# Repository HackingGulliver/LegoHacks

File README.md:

# LegoHacks
Alles rund um Lego und Elektronik.

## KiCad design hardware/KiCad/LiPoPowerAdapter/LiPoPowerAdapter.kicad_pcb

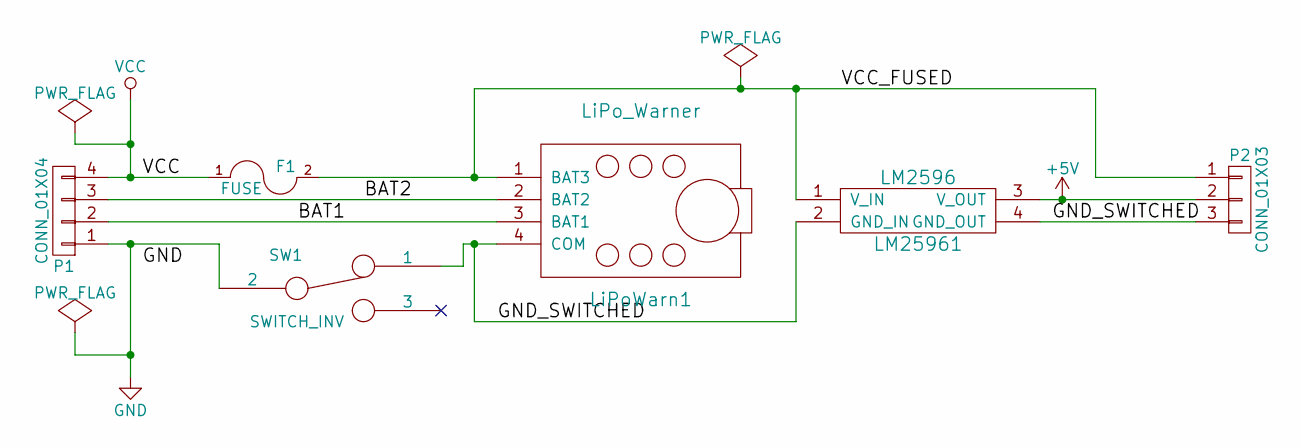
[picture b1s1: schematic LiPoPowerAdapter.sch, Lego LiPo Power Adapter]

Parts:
F1: FUSE; FKS-Halter
LM25961: LM2596
LiPoWarn1: LiPo_Warner; Pin_Header_Straight_1x04
P1: CONN_01X04; JST_XH_S04B-XH-A_04x2.50mm_Angled
P2: CONN_01X03; Pin_Header_Angled_1x03
SW1: SWITCH_INV; AS500APC-Kippschalter

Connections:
+5V: LM25961.3 (V_OUT), P2.2
/BAT1: LiPoWarn1.3 (BAT1), P1.2
/BAT2: LiPoWarn1.2 (BAT2), P1.3
/GND_SWITCHED: LM25961.2 (GND_IN), LM25961.4 (GND_OUT), LiPoWarn1.4 (COM), P2.3, SW1.1
/VCC_FUSED: F1.2, LM25961.1 (V_IN), LiPoWarn1.1 (BAT3), P2.1
GND: P1.1, SW1.2
VCC: F1.1, P1.4

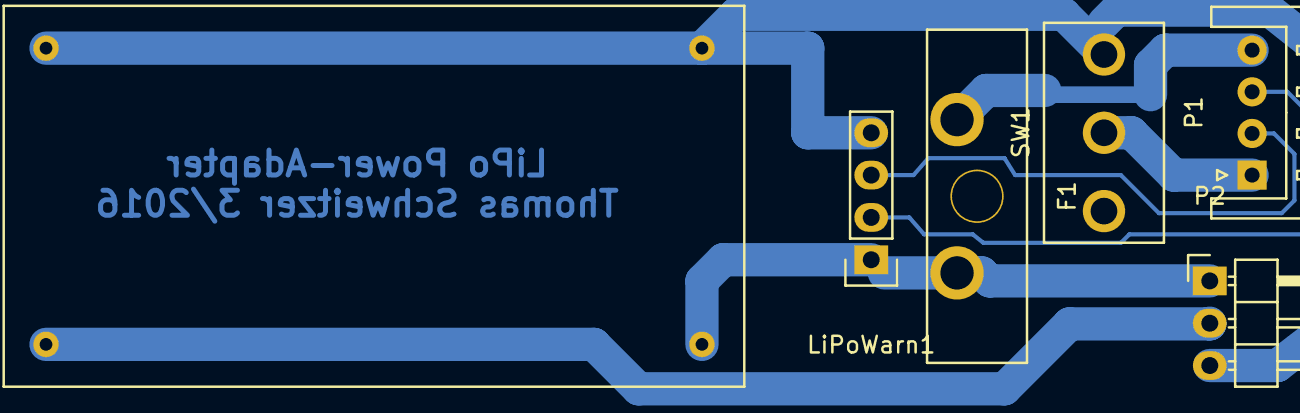
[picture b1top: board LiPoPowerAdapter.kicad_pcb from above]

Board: 2 copper layers, 6 parts (0 on the bottom side), 7 nets.

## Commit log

2016-02-25 Untertitel des Repos angepasst
2016-03-30 KiCad-Projekt mit LiPo-PowerAdapter hinzugefügt
2016-04-01 Erste Version der Stepper-Library zum Ansteuern von Schrittmotoren.
2016-04-01 LiPoPowerAdapter unter Linux mit KiCad bearbeitet
2016-04-03 Möglichkeit zum Debuggen hinzugefügt. Siehe geänderten Kommentar für eine Anleitung.
2016-04-05 Erste Version der SerialDriver-Hardware (KiCad) hinzugefügt
2016-04-05 .gitignore hinzugefügt
2016-04-05 SerialDriver Arduino-Projekt hinzugefügt
2016-04-05 Bauteil ULN2803 zur Bibliothek legohacks.lib hinzugefügt
2016-04-07 Erste Version des SerialDrivers mit Shift-Register und PWM. digitalWrite war sehr langsam und musste durch fastDigitalWrite ersetzt werden. Dies kann noch weiter optimiert werden.
2016-04-08 Optimierung beim Rausschreiben der Bits ins Schieberegister. Die Version ist ca. 14 mal schneller.
2016-04-08 Berechnung von PWM-Bitmustern für das Schieberegister in der Klasse PWMStateCalculator. Damit wird ein Lauflicht mit nachlassender Helligkeit realisiert.
2016-04-09 Shiftregister wird mittels SPI angesteuert
2016-04-09 Anpassungen für Benchmark mit SPI
2016-04-09 Anpassungen für Benchmark mit Bit Bang
2016-04-09 Überflüssigen Befehl entfernt
2016-04-09 Bit-Reihenfolge beim SPI-Transfer umgekehrt
2016-04-11 Aufruf der PWM-Schritte aus Timer heraus.
2016-04-12 Refaktorisierung mit neuen Methoden
2016-04-12 Erste Performance Messergebnisse
2016-04-12 Benchmarks und Optimierung für den PWMStateCalculator.
2016-04-13 Benchmarks zur Auswertung der Last durch die PWM-Timer erweitert.
2016-04-13 Benchmarks dokumentiert für Ist-Zustand und das Optimum, bei dem ohne Berechnung die Daten direkt gesendet werden.
2016-04-14 Erster Entwurf des vorberechnenden PWMStateCalculators
2016-04-15 Fine-Tuning am Algorithmus zur Berechnung der zu sendenden Daten.
2016-04-15 Funktionierende Version des vorberechnenden State-Calculators
2016-04-15 Benchmarks in eigene Datei ausgelagert.
2016-04-15 Optimierung des vorberechnenden PWMStateCalculators. (Version 2 in den Benchmarks).
2016-04-16 Benchmark zur Messung der Zeit in der die zu sendenden Daten berechnet werden.
2016-04-16 Berechnung der Daten optimiert (im Benchmark Version 3)
2016-04-16 Schleife zur Berechnung der Daten optimiert (Version 4)
2016-04-16 Commented and cleaned up the code. Moved some initialization to the PWMStateCalculator.
2016-04-16 RGB-LED Test
2016-04-16 Bitreihenfolge im PWMStateCalculator geändert.
2016-04-18 Die zu sendenden Daten werden jeweils nur für den aktuellen Schritt vorberechnet, falls Duty-Einstellungen geändert wurden.
2016-04-19 Die Klassen PWMController und PowerController wurden hinzugefügt. Der PWMController übernimmt das Setup des Timers und steuert damit den PWMStateCalculator an.
2016-04-19 Die Methoden setDuty() und allDutiesSet() werden nun direkt vom PowerController implementiert. Sie delegieren an den chainedController.
2016-04-19 Klasse RGBLed hinzugefügt.
2016-04-19 Erste Version mit MsTimer2 zur Ansteuerung des TimedPowerControllers
2016-04-19 TimedPowerController als abstrakte Klasse und Pulse als eine konkrete Implementierung hinzugefügt. Pulse ist bisher nur rudimentär.
2016-04-25 Erste Version des TimerPowerControllers "Pulse" mit Fixed Point Arithmetic
2016-04-25 Pulse mit Dreieckssignal und wenigen floating point Berechnungen.
2016-04-26 Pulsweite kann in der Klasse Pulse gesetzt werden.
2016-04-26 Pulse unterstützt die Wellenformen Sägezahn, Dreieck und Blinken.
2016-04-27 Code cleanup in Klasse Pulse
2016-06-02 Im Beispielprogramm vom SerialDriver wird nach der Änderung der LED-Farbe die Pulsweite gesetzt, damit die Änderungen wirksam werden.
2016-06-02 Neue Projekte zum Experimentieren mit der VirtualWire-Lib hinzugefügt. Senden und Empfangen mit dem mitgelieferten Beispielcode ist damit möglich.
2016-06-07 Initiale Version des VirtualWireReceivers mit TimerOne als Basis-Lib für Timer
2016-06-07 VirtualWire-Lib umgestellt auf TimerOne. Siehe vw_setupTO().
2016-06-11 Erweiterung des seriellen PWM Controllers um einen TimerShare, mit dem Timer1 auch für andere Zwecke benutzt werden kann.
2016-06-11 Umbau der VirtualWire-Library, so dass die Timer-Callbackmethode auch von anderen Quellen aufgerufen werden kann.
2016-06-11 VirtualWire benutzt Timer1 vom seriellen PWM Controller.
2016-06-11 VirtualWireReceiver gibt aus, wieviele Nachrichten pro Sekunden empfangen wurden.
2016-06-12 Erweiterung des seriellen PWMControllers um einen TimerShare mit dem auch andere Funktionen in Timer1 aufgerufen werden können.
2016-06-12 TimerShare ins Originalproject SerialDriver übernommen.
2016-06-12 Abfrage des RX-Pins in VirtualWire direkt über das Arduino Pin-Register statt über digitalRead()
2016-06-12 Projekt umorganisiert: Klassen für die serielle PWM-Steuerung ins Verzeichnis myLibs/SerialPWM verschoben.
2016-06-12 Projekt VirtualWireWithTimerOne nach Branch develop übernommen. Meine Version der VirtualWire-Lib nach myLibs/VirtualWireTimerOne übernommen.
2016-06-13 Erste Version des MovingStartPWMStateCalculator
2016-06-14 Fast richtige Berechnung der PWM-Daten
2016-06-14 Korrekte Version des MovingStartStateCalculator
2016-06-14 Fix im MovingStartStateCalculator für PWM-Wert = 255
2016-06-14 Geändertes LED-Muster im SerialDriver-Hauptprogramm
2020-05-02 Satz beendet
